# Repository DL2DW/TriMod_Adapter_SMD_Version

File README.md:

# TriMod Adapter (SMD Version)

## IEEE-488 for the Commodore 1541 Disk Drive

Before I developed the [version with normal THT components](https://github.com/DL2DW/TriMod_Adapter), I built a version with SMD components. 

Only the integrated Kernal adapter is missing. This must be plugged in externally additionally.

# Technical

Commodore had derived the 2031LP from the 1541 at that time. If you look at both schematics, they only differ in one detail.

And this is the connection to the outside world. 

On the 1541, the VIA 6522 is only partially used, because port A is not connected. Port B provides the lines for the CBM bus, which communicate with the computer via a 74LS14 and 74LS06 driver.

In contrast, port A is also required for the 2031LP. This provides the 8 parallel data lines, while port B is responsible for the control lines of the GPIB bus. Here the two drivers SN75160 and SN75161 are used.

And these are basically the actual differences, to put it simply.

So the 1541 can be easily converted to a 2031 with an adapter board. Of course, the Kernal has to be exchanged accordingly.

So that the adapter does not have to be removed every time you want to use the CBM bus, I have made the whole switchable.

With the help of CD4066 4-fold switches, the lines can be easily switched. A connector for switching a Kernal adapter is also available.

The IEEE-488 connector is clearly visible on the left side. This can either be led out with a ribbon cable or connected to a corresponding socket in the case. 

The two pin headers at the bottom are for the connection to the kernel adapter and the switch itself. 

- Contact 1 = GND
- Contact 2 = RESET
- Contact 3 = Kernel switch
- Contact 4 & 5 = Switching between IEC and IEEE-488

A standard switch is connected to contact 4 & 5. Connecting the two contacts switches to IEEE-488 mode. Contact 3 is used to switch the kernel then as well. This contact is connected to the above mentioned kernel adapter board.

A 27128 EPROM is required for the Kernal. First (address 0x0000) the binary for the 1541 mode is written and afterwards (address 0x2000) the binary for the IEEE-488 mode.

With setting the jumper the mode can be switched. Of course this should be done only in the switched off state.

# BOM

Here is the list of components. 

|      | Description                                                  | Part                  | References           | Value                       | Quantity Per PCB |
| ---- | ------------------------------------------------------------ | --------------------- | -------------------- | --------------------------- | ---------------- |
| 1    | Unpolarized capacitor                                        | C                     | C1 C2 C3 C4 C5 C6 C7 | 100nF                       | 7                |
| 2    | Generic connector, single row, 01x03, script generated (kicad-library-utils/schlib/autogen/connector/) | Conn_01x03            | CN1                  | Kernal                      | 1                |
| 3    | Diode                                                        | D                     | D1 D2                | 1N4148                      | 2                |
| 4    | Generic connector, double row, 02x12, top/bottom pin numbering scheme (row 1: 1...pins_per_row, row2: pins_per_row+1 ... num_pins), script generated (kicad-library-utils/schlib/autogen/connector/) | Conn_02x12_Top_Bottom | J3                   | IEEE-488 Connector          | 1                |
| 5    | Generic connector, single row, 01x20, script generated (kicad-library-utils/schlib/autogen/connector/) | Conn_01x20            | J1 J2                | PIN Header to PCB 6522 1-20 | 2                |
| 6    | Jumper, 2-pole, open                                         | Jumper_2_Open         | JP1                  | Jumper                      | 1                |
| 7    | Resistor                                                     | R                     | R3                   | 10k                         | 1                |
| 8    | Resistor                                                     | R                     | R4                   | 1k                          | 1                |
| 9    | Resistor                                                     | R                     | R1 R2 R5             | 3k3                         | 3                |
| 10   | 2x DIP Switch, Single Pole Single Throw (SPST) switch, small symbol | SW_DIP_x02            | SW1                  | IEEE-488 Device ID          | 1                |
| 11   | Quad Analog Switches                                         | 4066                  | U1 U2                | 4066                        | 2                |
| 12   |                                                              | 7406N                 | U7                   | 7406N                       | 1                |
| 13   | Quad 2-input XOR                                             | 74LS86                | U3                   | 74LS86                      | 1                |
| 14   |                                                              | MOS6522               | U4                   | MOS6522                     | 1                |
| 15   |                                                              | SN75160               | U5                   | SN75160                     | 1                |
| 16   |                                                              | SN75161               | U6                   | SN75161                     | 1                |

# PCB

The PCB can either be ordered directly from [PCBWay](https://www.pcbway.com/project/shareproject/TriMod_Adapter_SMD_Version.html), or you can create it yourself from the Gerber files available here.

If you liked my project, I would be very happy about a small coffee donation.

# License

The contents of this repository are released under the following license:

- the "Creative Commons Attribution-NonCommercial-ShareAlike 4.0 International License" (CC BY-NC-SA 4.0) full text of this license is included in the [LICENSE.CC-NC-BY-SA-4.0](https://github.com/DL2DW/TriMod_Adapter_SMD_Version/blob/main/LICENSE.CC-NC-BY-SA) file and a copy can also be found at https://creativecommons.org/licenses/by-nc-sa/4.0/

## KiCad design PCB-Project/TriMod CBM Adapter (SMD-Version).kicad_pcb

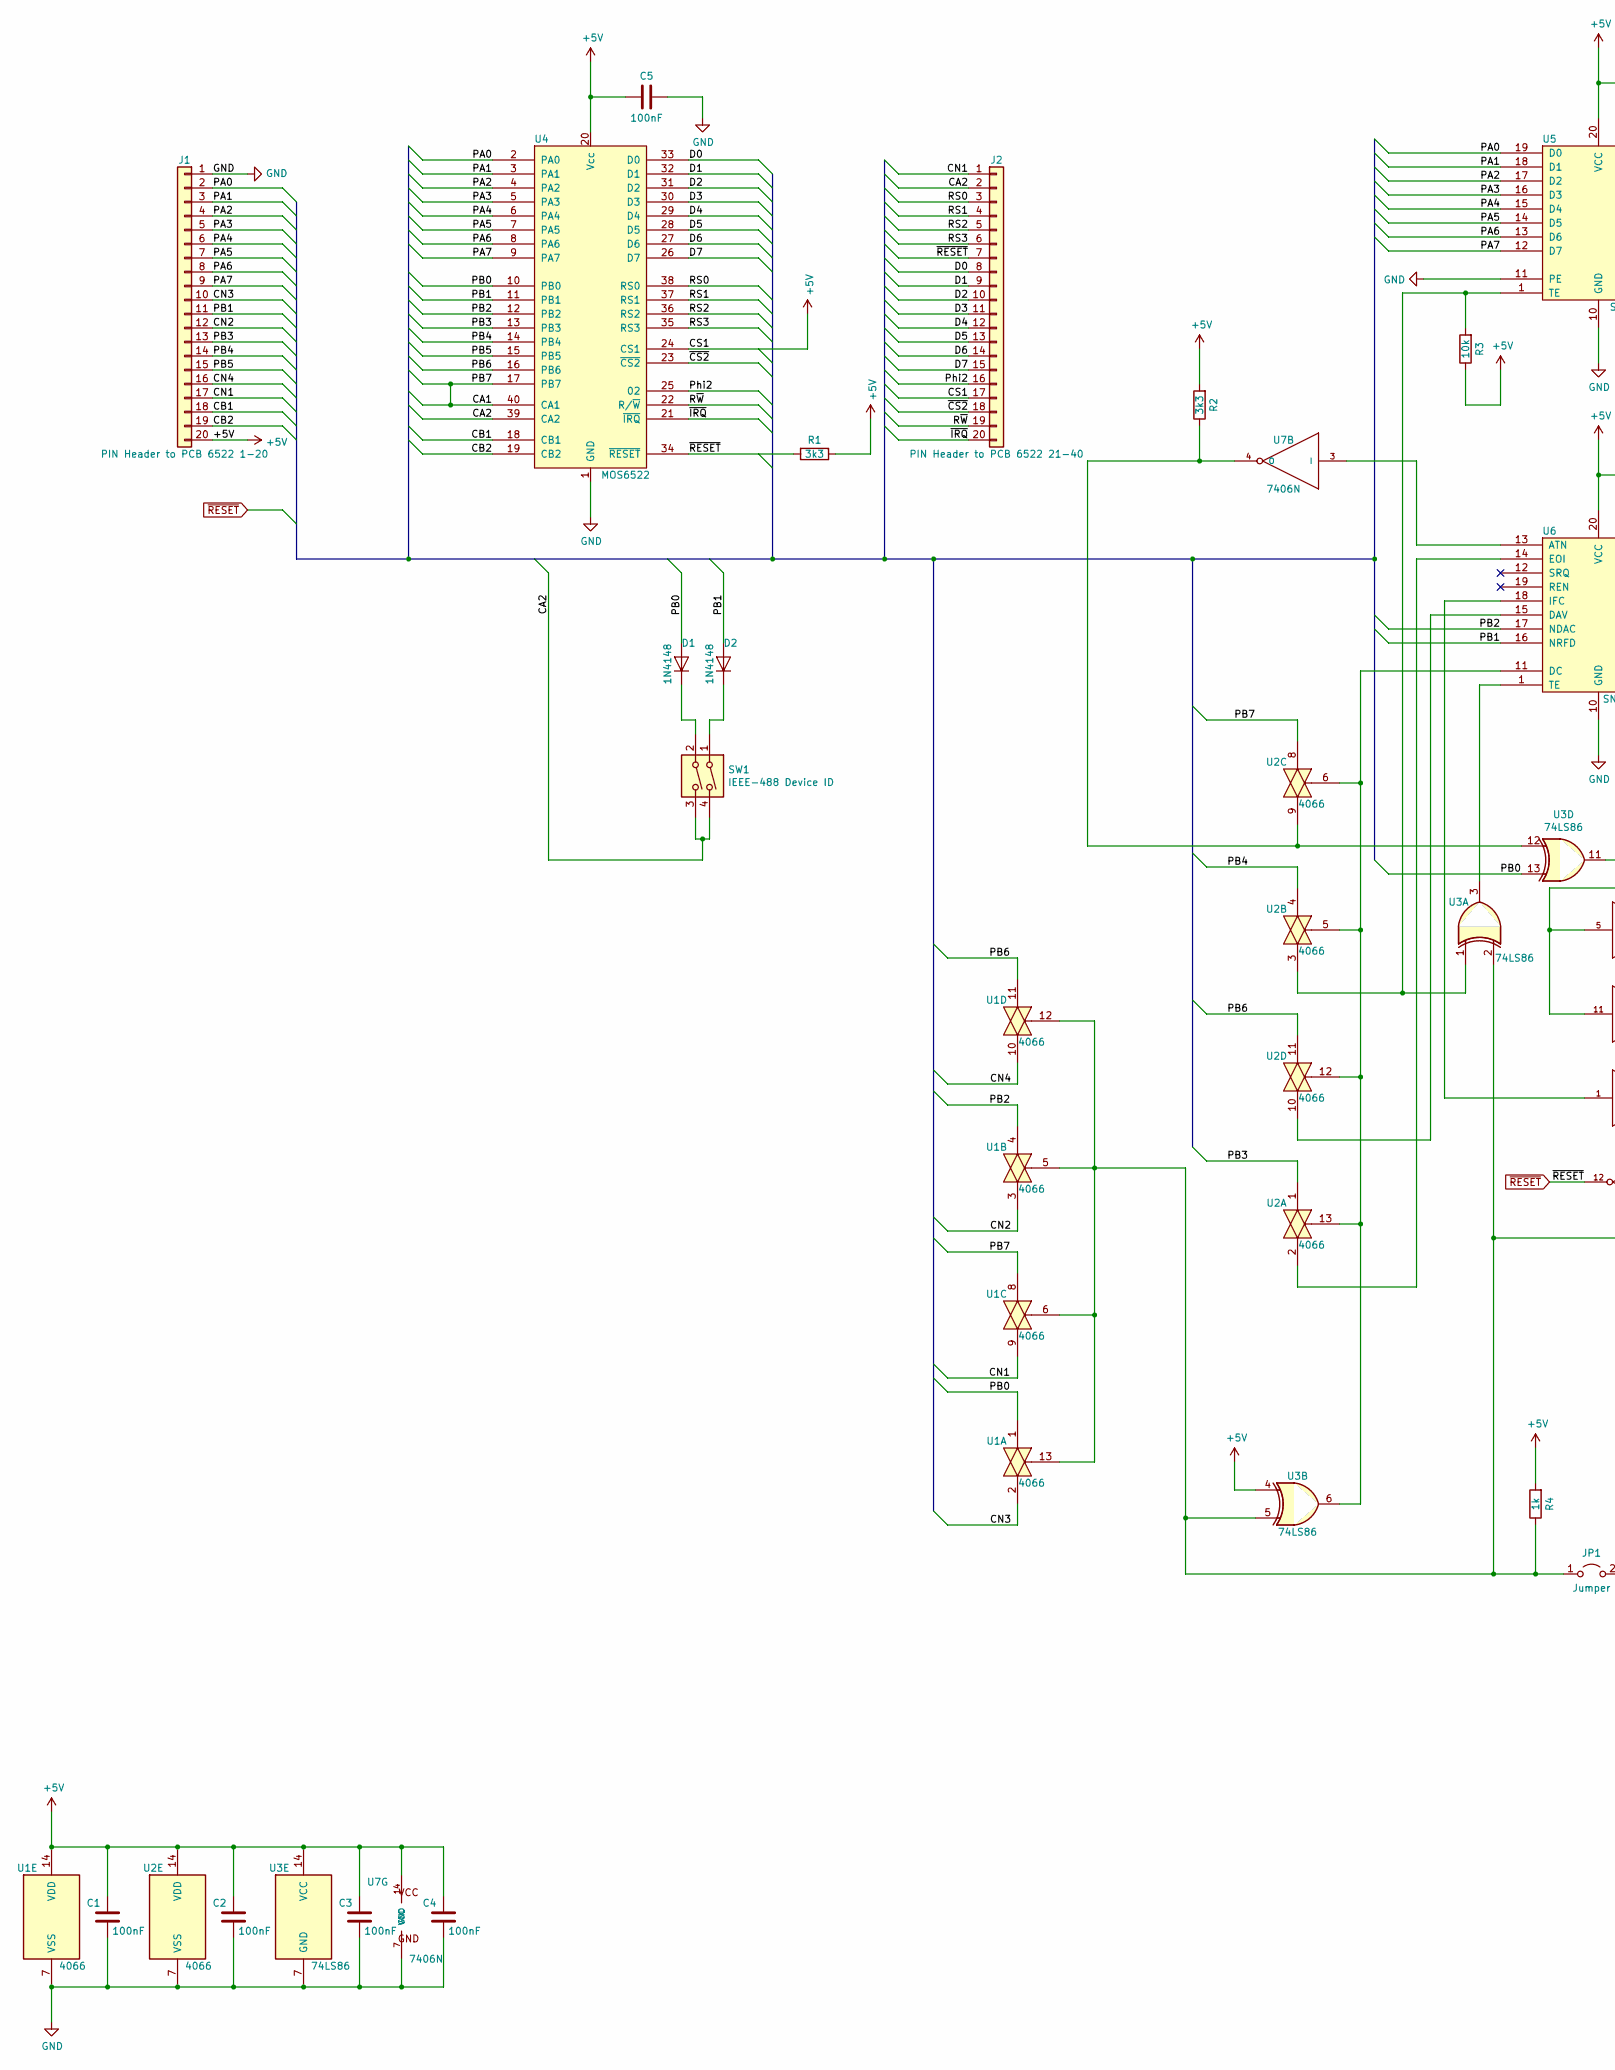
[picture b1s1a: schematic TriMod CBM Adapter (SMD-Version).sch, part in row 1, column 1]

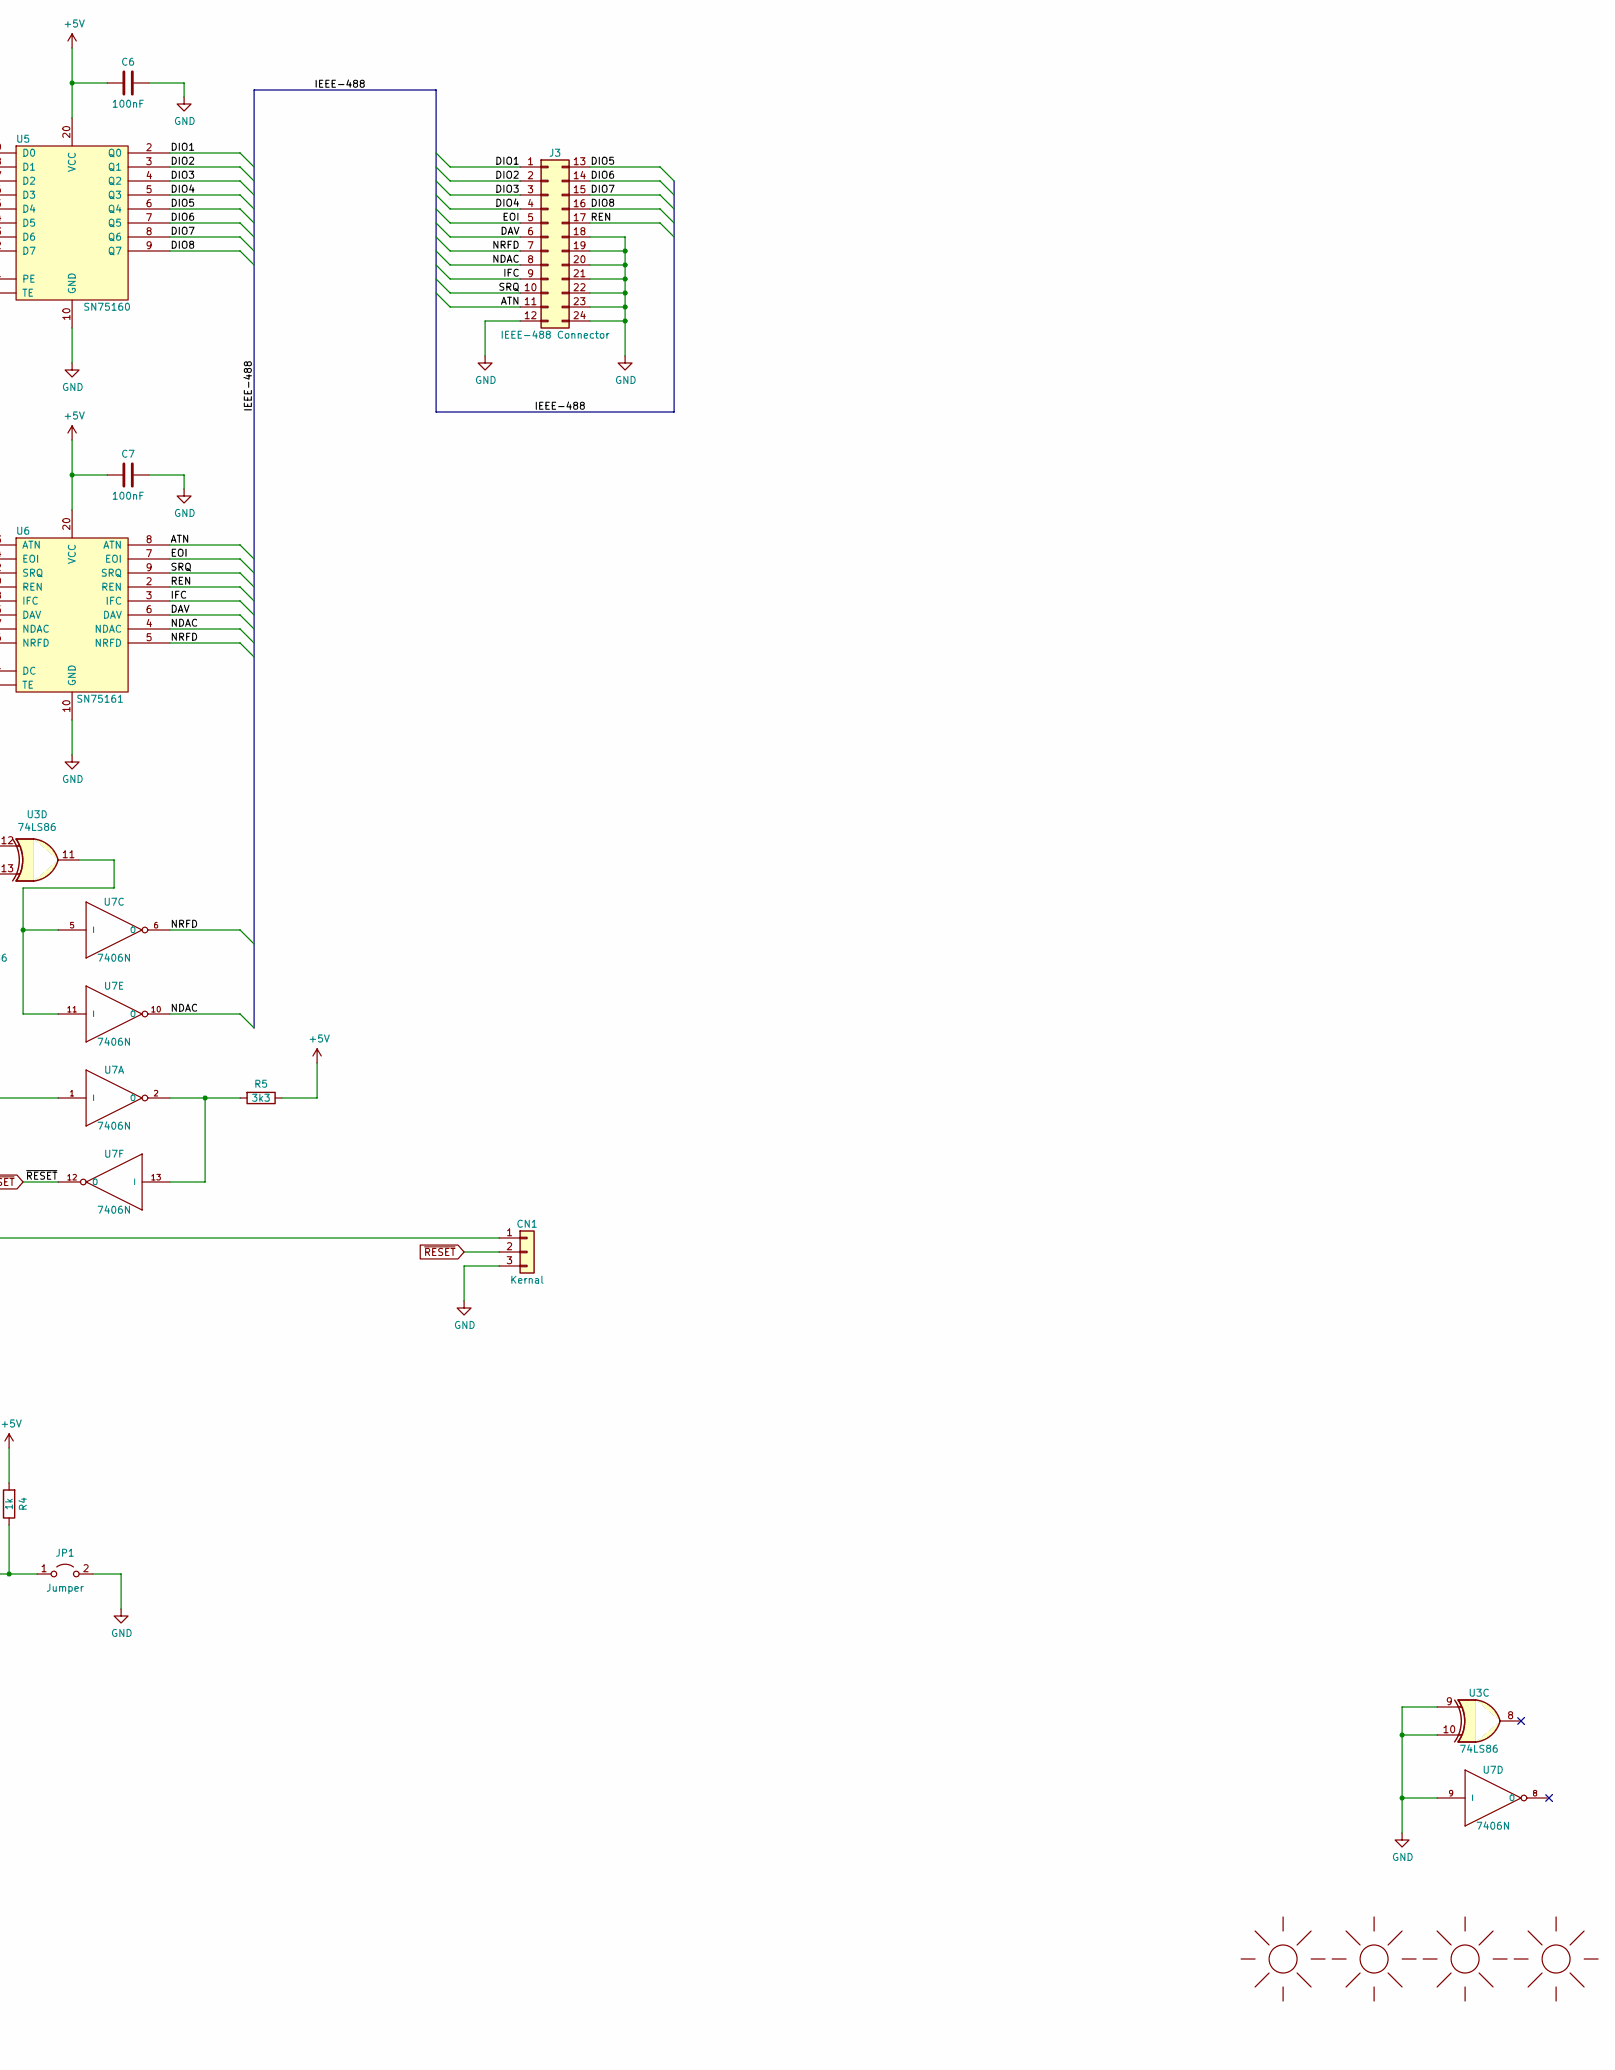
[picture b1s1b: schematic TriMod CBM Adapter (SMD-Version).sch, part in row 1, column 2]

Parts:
C1, C2, C3, C4, C5, C6, C7: 100nF; C_0603_1608Metric
CN1: Kernal; PinHeader_1x03_P2.54mm_Vertical
D1, D2: 1N4148; D_MiniMELF
J1: PIN Header to PCB 6522 1-20; PinHeader_1x20_P2.54mm_Vertical
J2: PIN Header to PCB 6522 21-40; PinHeader_1x20_P2.54mm_Vertical
J3: IEEE-488 Connector; PinHeader_2x12_P2.54mm_Top_Bottom_Vertical_Mirror
JP1: Jumper; PinHeader_1x02_P2.54mm_Vertical
M1: SUNLOGO; DL2DW_Logo_Silk_20x10mm
M2: SUNLOGO; KiCad-Logo2_8mm_SilkScreen
M3: SUNLOGO; OSHW-Logo2_9.8x8mm_SilkScreen
M4: SUNLOGO; Logo_silk_CC-BY-NC-SA_10x3.6mm
R1, R2, R5: 3k3; R_0805_2012Metric
R3: 10k; R_0805_2012Metric
R4: 1k; R_0805_2012Metric
SW1: IEEE-488 Device ID; dip_2-300
U1, U2: 4066; SOIC-14_3.9x8.7mm_P1.27mm
U3: 74LS86; SOIC-14_3.9x8.7mm_P1.27mm
U4: MOS6522; dil_40-600_socket
U5: SN75160; SO-20_12.8x7.5mm_P1.27mm
U6: SN75161; SO-20_12.8x7.5mm_P1.27mm
U7: 7406N; SOIC-14_3.9x8.7mm_P1.27mm

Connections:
+5V: C1.2, C2.2, C3.2, C4.2, C5.2, C6.2, C7.2, J1.20, J2.17, R1.1, R2.2, R3.1, R4.2, R5.1, U1.14 (VDD), U2.14 (VDD), U3.4, U3.14 (VCC), U4.20 (Vcc), U4.24 (CS1), U5.20 (VCC), U6.20 (VCC), U7.14 (VCC)
/ATN: J3.11, U6.8 (ATN)
/CA1: U1.8, U2.8, U4.17 (PB7), U4.40 (CA1)
/CA2: J2.2, SW1.3, SW1.4, U4.39 (CA2)
/CB1: J1.18, U4.18 (CB1)
/CB2: J1.19, U4.19 (CB2)
/CN1: J1.17, J2.1, U1.9
/CN2: J1.12, U1.3
/CN3: J1.10, U1.2
/CN4: J1.16, U1.10
/D0: J2.8, U4.33 (D0)
/D1: J2.9, U4.32 (D1)
/D2: J2.10, U4.31 (D2)
/D3: J2.11, U4.30 (D3)
/D4: J2.12, U4.29 (D4)
/D5: J2.13, U4.28 (D5)
/D6: J2.14, U4.27 (D6)
/D7: J2.15, U4.26 (D7)
/DAV: J3.6, U6.6 (DAV)
/DIO1: J3.1, U5.2 (Q0)
/DIO2: J3.2, U5.3 (Q1)
/DIO3: J3.3, U5.4 (Q2)
/DIO4: J3.4, U5.5 (Q3)
/DIO5: J3.13, U5.6 (Q4)
/DIO6: J3.14, U5.7 (Q5)
/DIO7: J3.15, U5.8 (Q6)
/DIO8: J3.16, U5.9 (Q7)
/EOI: J3.5, U6.7 (EOI)
/IFC: J3.9, U6.3 (IFC)
/NDAC: J3.8, U6.4 (NDAC), U7.10 (O)
/NRFD: J3.7, U6.5 (NRFD), U7.6 (O)
/PA0: J1.2, U4.2 (PA0), U5.19 (D0)
/PA1: J1.3, U4.3 (PA1), U5.18 (D1)
/PA2: J1.4, U4.4 (PA2), U5.17 (D2)
/PA3: J1.5, U4.5 (PA3), U5.16 (D3)
/PA4: J1.6, U4.6 (PA4), U5.15 (D4)
/PA5: J1.7, U4.7 (PA5), U5.14 (D5)
/PA6: J1.8, U4.8 (PA6), U5.13 (D6)
/PA7: J1.9, U4.9 (PA7), U5.12 (D7)
/PB0: D1.2 (A), U1.1, U3.13, U4.10 (PB0)
/PB1: D2.2 (A), J1.11, U4.11 (PB1), U6.16 (NRFD)
/PB2: U1.4, U4.12 (PB2), U6.17 (NDAC)
/PB3: J1.13, U2.1, U4.13 (PB3)
/PB4: J1.14, U2.4, U4.14 (PB4)
/PB5: J1.15, U4.15 (PB5)
/PB6: U1.11, U2.11, U4.16 (PB6)
/Phi2: J2.16, U4.25 (02)
/REN: J3.17, U6.2 (REN)
/RS0: J2.3, U4.38 (RS0)
/RS1: J2.4, U4.37 (RS1)
/RS2: J2.5, U4.36 (RS2)
/RS3: J2.6, U4.35 (RS3)
/R~W: J2.19, U4.22 (R/~W)
/SRQ: J3.10, U6.9 (SRQ)
/~CS2: J2.18, U4.23 (~CS2)
/~IRQ: J2.20, U4.21 (~IRQ)
GND: C1.1, C2.1, C3.1, C4.1, C5.1, C6.1, C7.1, CN1.3, J1.1, J3.12, J3.18, J3.19, J3.20, J3.21, J3.22, J3.23, J3.24, JP1.2 (B), U1.7 (VSS), U2.7 (VSS), U3.7 (GND), U3.9, U3.10, U4.1 (GND), U5.10 (GND), U5.11 (PE), U6.10 (GND), U7.7 (GND), U7.9 (I)
unnamed: CN1.1, JP1.1 (A), R4.1, U1.5, U1.6, U1.12, U1.13, U3.2, U3.5
unnamed: D1.1 (K), SW1.2
unnamed: D2.1 (K), SW1.1
unnamed: R2.1, U2.9, U3.12, U7.4 (O)
unnamed: R3.2, U2.3, U3.1, U5.1 (TE)
unnamed: R5.2, U7.2 (O), U7.13 (I)
unnamed: U2.2, U6.14 (EOI)
unnamed: U2.10, U6.15 (DAV)
unnamed: U2.5, U2.6, U2.12, U2.13, U3.6, U6.11 (DC)
unnamed: U3.3, U6.1 (TE)
unnamed: U3.11, U7.5 (I), U7.11 (I)
unnamed: U6.13 (ATN), U7.3 (I)
unnamed: U6.18 (IFC), U7.1 (I)
~RESET: CN1.2, J2.7, R1.2, U4.34 (~RESET), U7.12 (O)

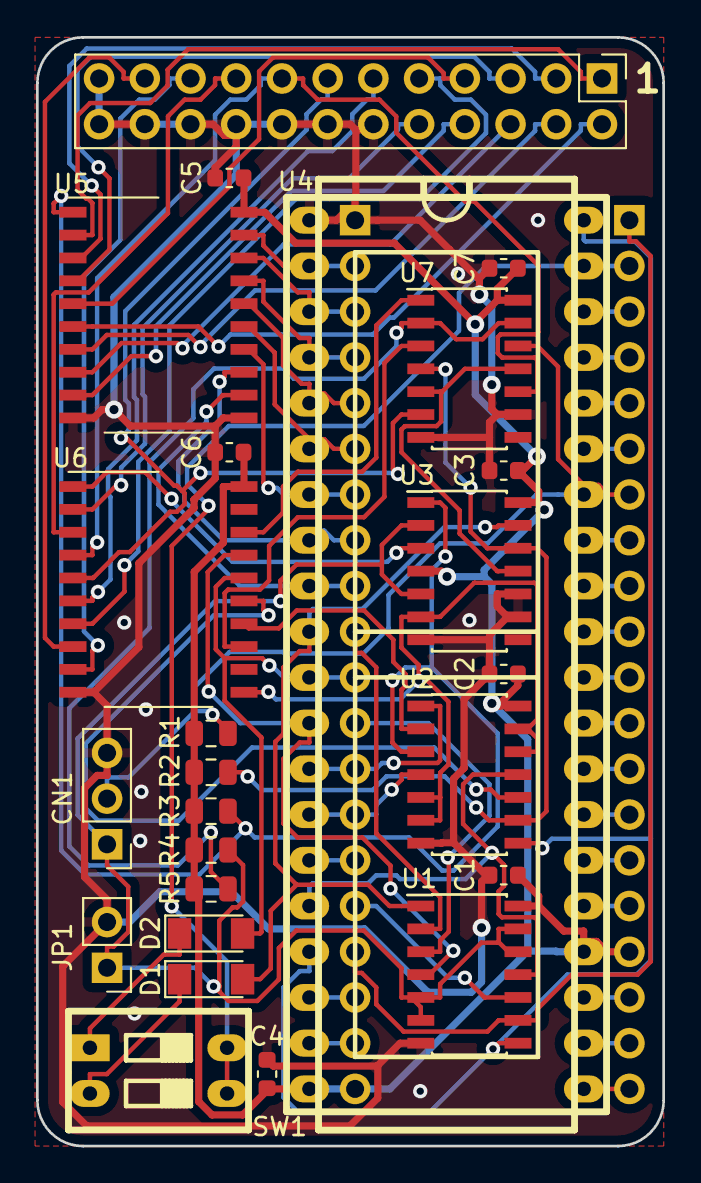
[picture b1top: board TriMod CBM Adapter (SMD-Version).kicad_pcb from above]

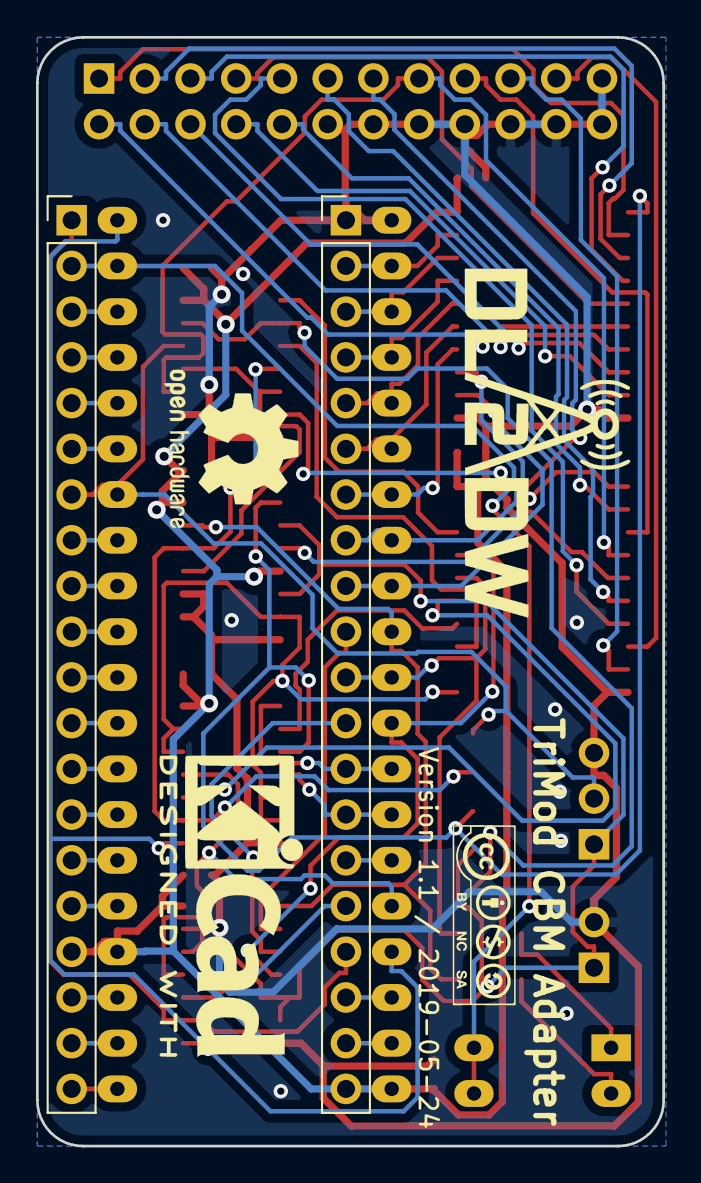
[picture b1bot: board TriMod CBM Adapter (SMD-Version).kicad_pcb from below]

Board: 2 copper layers, 34.8 x 61.6 mm, 31 parts (6 on the bottom side), 71 nets.

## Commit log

2021-01-11 IEEE-488 Kernal added
2021-01-11 PCB order link added
